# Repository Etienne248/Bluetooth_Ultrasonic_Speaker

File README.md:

## Bluetooth Phased Array Directional Speaker

This repository contains the source code and hardware schematics for a Bluetooth phased array directional speaker built using ESP32 and ESP-IDF.

The project aims to create a speaker that can project a beam of sound in a specific direction using a phased array, allowing for a more targeted listening experience. The speaker is connected via Bluetooth to any compatible device, such as a smartphone or laptop.

<!--  

 -->

<table>
  <tr>
    <td></td>
    <td></td>
  </tr>
  <tr>
    <td></td>
    <td></td>
  </tr>
</table>

## Installation and Usage

To use this project, you will need an ESP32 development board and the ESP-IDF development framework installed on your machine. You can find instructions for installing ESP-IDF with PlatformIO [here](https://docs.platformio.org/en/latest/plus/debugging.html#advanced-configuration).

Once you have ESP-IDF installed with PlatformIO, you can clone this repository and open it in Visual Studio Code with the PlatformIO extension. From there, you can build and flash the firmware to your ESP32 board using the PlatformIO toolbar.

The code for the project can be found in the `Code_Phased_Array_Speaker_esp_idf` directory, and the KiCad files for the hardware can be found in the `Kicad_Phased_Array_Speaker` directory.

After flashing the firmware, you can connect your Bluetooth device to the speaker and begin playing audio. The speaker will project sound in the direction indicated by the phased array.

## Project Structure

The project is organized as follows:

- `Code_Phased_Array_Speaker_esp_idf` directory contains the main application code
- `Kicad_Phased_Array_Speaker` directory contains the hardware schematics and PCB layout files

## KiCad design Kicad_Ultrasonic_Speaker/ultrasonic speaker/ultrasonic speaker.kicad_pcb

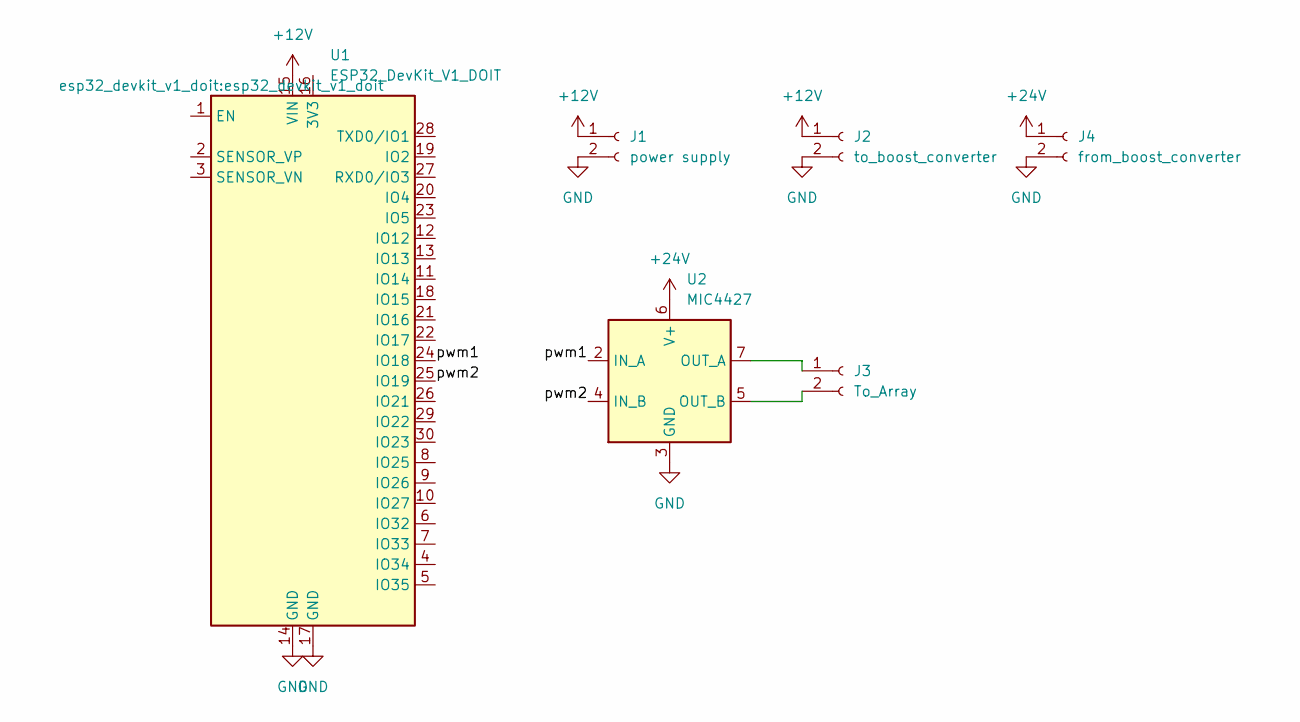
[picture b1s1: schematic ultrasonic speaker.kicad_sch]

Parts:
J1: power supply; TerminalBlock_Phoenix_MKDS-1,5-2_1x02_P5.00mm_Horizontal
J2: to_boost_converter; TerminalBlock_Phoenix_MKDS-1,5-2_1x02_P5.00mm_Horizontal
J3: To_Array; TerminalBlock_Phoenix_MKDS-1,5-2_1x02_P5.00mm_Horizontal
J4: from_boost_converter; TerminalBlock_Phoenix_MKDS-1,5-2_1x02_P5.00mm_Horizontal
U1: ESP32_DevKit_V1_DOIT; esp32_devkit_v1_doit
U2: MIC4427; Fet_driver_SOIC-8-1EP_3.9x4.9mm_P1.27mm_EP2.29x3mm

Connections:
+12V: J1.1, J2.1, U1.15 (VIN)
+24V: J4.1, U2.6 (V+)
/pwm1: U1.24 (IO18), U2.2 (IN_A)
/pwm2: U1.25 (IO19), U2.4 (IN_B)
GND: J1.2, J2.2, J4.2, U1.14 (GND), U1.17 (GND), U2.3 (GND)
unnamed: J3.1, U2.7 (OUT_A)
unnamed: J3.2, U2.5 (OUT_B)

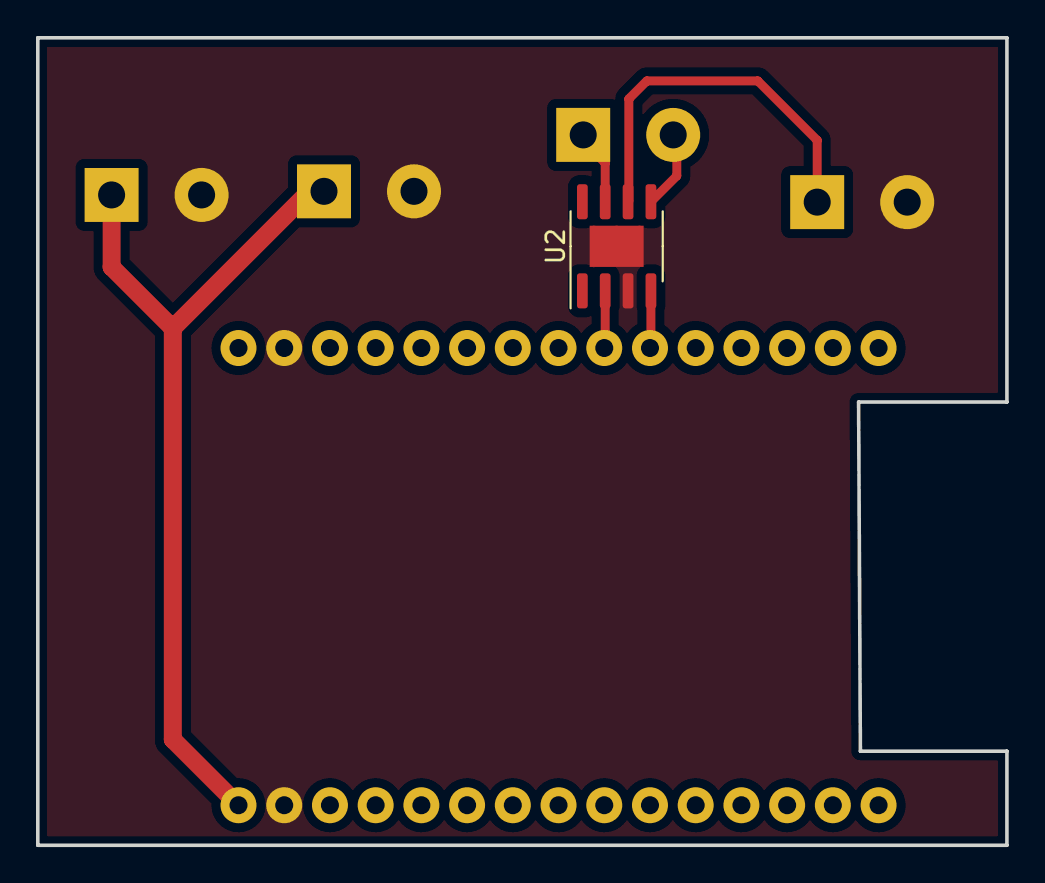
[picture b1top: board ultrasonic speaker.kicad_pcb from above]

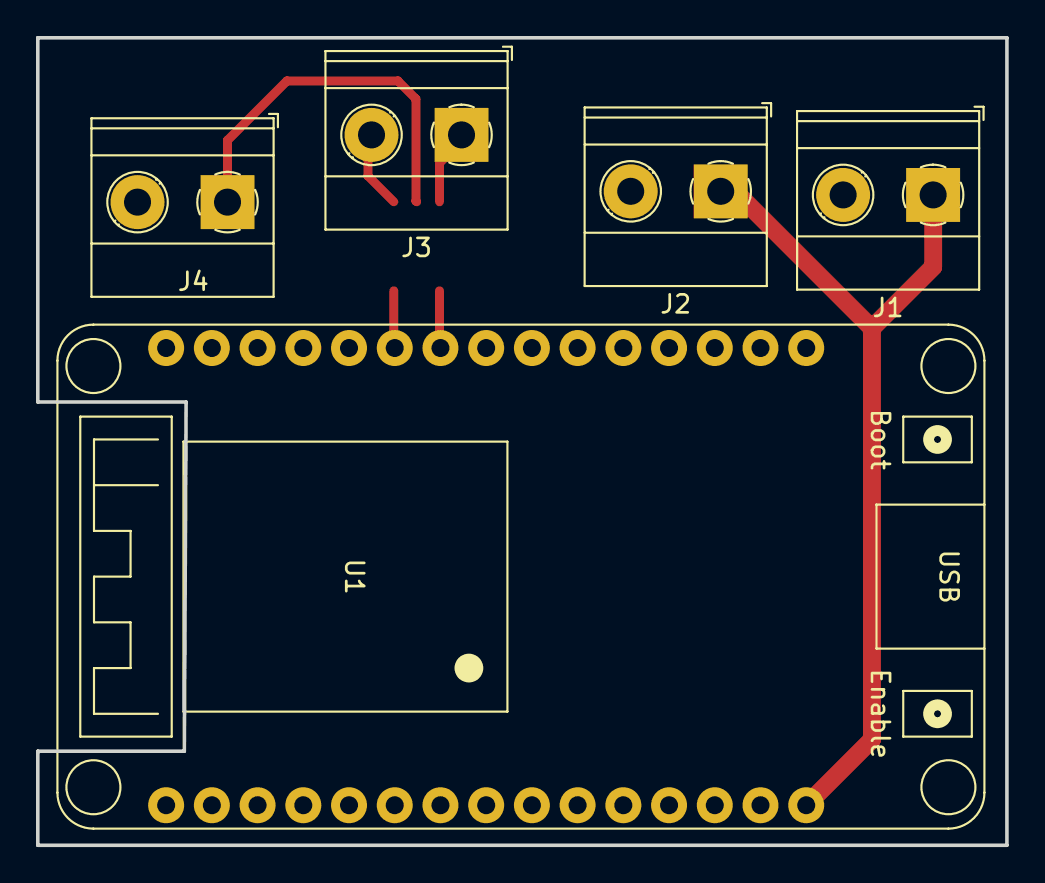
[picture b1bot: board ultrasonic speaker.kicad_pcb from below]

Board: 2 copper layers, 53.8 x 44.9 mm, 6 parts (5 on the bottom side), 7 nets.

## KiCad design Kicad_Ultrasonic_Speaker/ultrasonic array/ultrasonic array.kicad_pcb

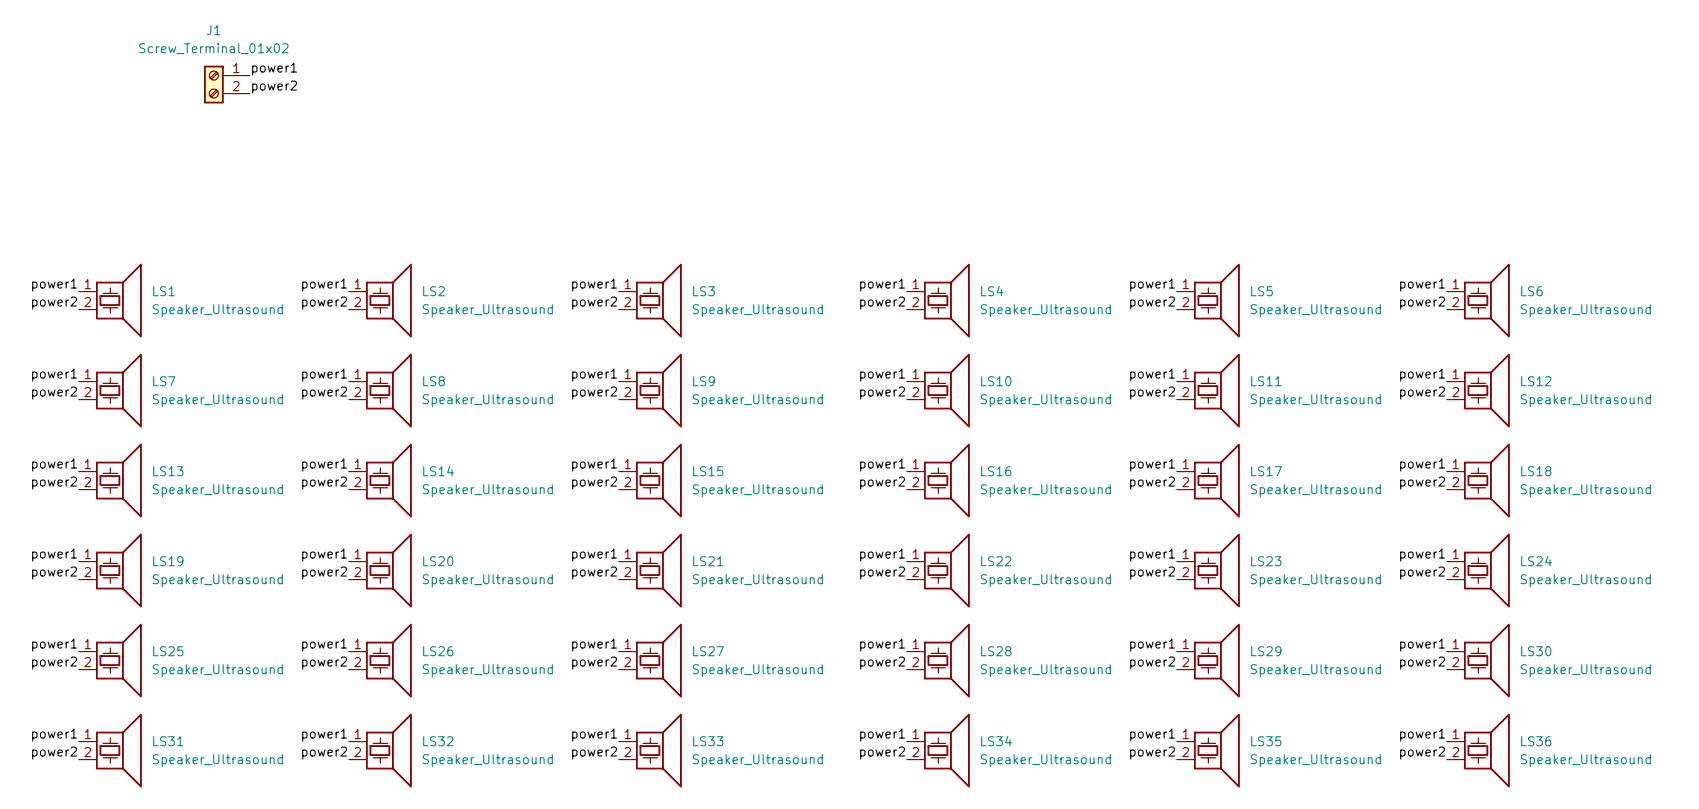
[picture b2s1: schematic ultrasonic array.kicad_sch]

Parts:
J1: Screw_Terminal_01x02; TerminalBlock_Phoenix_MKDS-1,5-2_1x02_P5.00mm_Horizontal
LS1, LS2, LS3, LS4, LS5, LS6, LS7, LS8, LS9, LS10, LS11, LS12, LS13, LS14, LS15, LS16, LS17, LS18, LS19, LS20, LS21, LS22, LS23, LS24, LS25, LS26, LS27, LS28, LS29, LS30, LS31, LS32, LS33, LS34, LS35, LS36: Speaker_Ultrasound; ultrasonic_D16mm_P10mm

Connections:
/power1: J1.1, LS1.1, LS2.1, LS3.1, LS4.1, LS5.1, LS6.1, LS7.1, LS8.1, LS9.1, LS10.1, LS11.1, LS12.1, LS13.1, LS14.1, LS15.1, LS16.1, LS17.1, LS18.1, LS19.1, LS20.1, LS21.1, LS22.1, LS23.1, LS24.1, LS25.1, LS26.1, LS27.1, LS28.1, LS29.1, LS30.1, LS31.1, LS32.1, LS33.1, LS34.1, LS35.1, LS36.1
/power2: J1.2, LS1.2, LS2.2, LS3.2, LS4.2, LS5.2, LS6.2, LS7.2, LS8.2, LS9.2, LS10.2, LS11.2, LS12.2, LS13.2, LS14.2, LS15.2, LS16.2, LS17.2, LS18.2, LS19.2, LS20.2, LS21.2, LS22.2, LS23.2, LS24.2, LS25.2, LS26.2, LS27.2, LS28.2, LS29.2, LS30.2, LS31.2, LS32.2, LS33.2, LS34.2, LS35.2, LS36.2

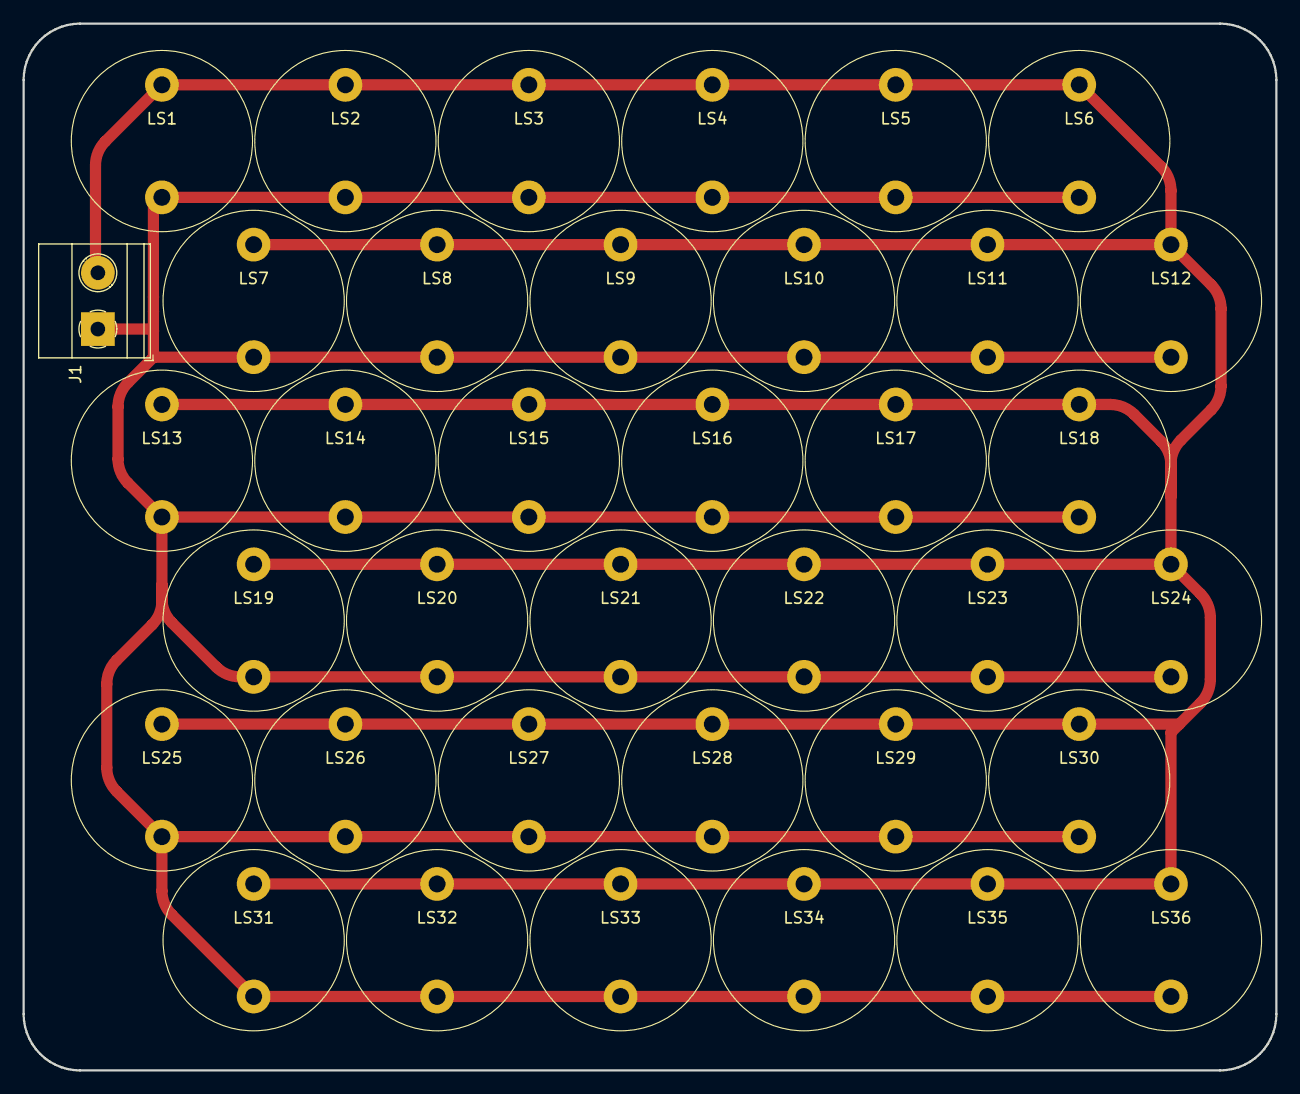
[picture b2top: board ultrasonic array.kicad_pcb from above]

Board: 2 copper layers, 111.3 x 93.0 mm, 37 parts (0 on the bottom side), 2 nets.

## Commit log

2023-02-15 add interupt
2023-02-16 cpu configue
2023-02-17 separate function
2023-02-17 bluetooth test
2023-02-28 source and header for pwm
2023-02-28 documentation
2023-03-01 bug corection
2023-03-01 add bluetooth
2023-03-01 add pwm ringbuffer
2023-03-01 change of duty cycle according to bluetooth data
2023-03-02 test for debug
2023-03-02 first comit on the branch
2023-03-03 change main
2023-03-03 so it is 16 bits for each side
2023-03-03 finish?
2023-03-03 chang angle
2023-03-08 add_kicad_file
2023-03-09 change kicad
2023-03-10 try flatCAM
2023-03-10 kicad 6.0
2023-03-15 hole enlargement
2023-03-22 change for boost converter
2023-03-22 simple save
2023-03-22 add soldering mask
2023-03-23 modification of esp32 pcb
2023-03-26 add multy_mask_pdf
2023-03-26 clean code folder
2023-04-07 Create LICENSE
2024-01-09 add images
2024-10-16 correction README.md
2024-12-08 add presentation slide
